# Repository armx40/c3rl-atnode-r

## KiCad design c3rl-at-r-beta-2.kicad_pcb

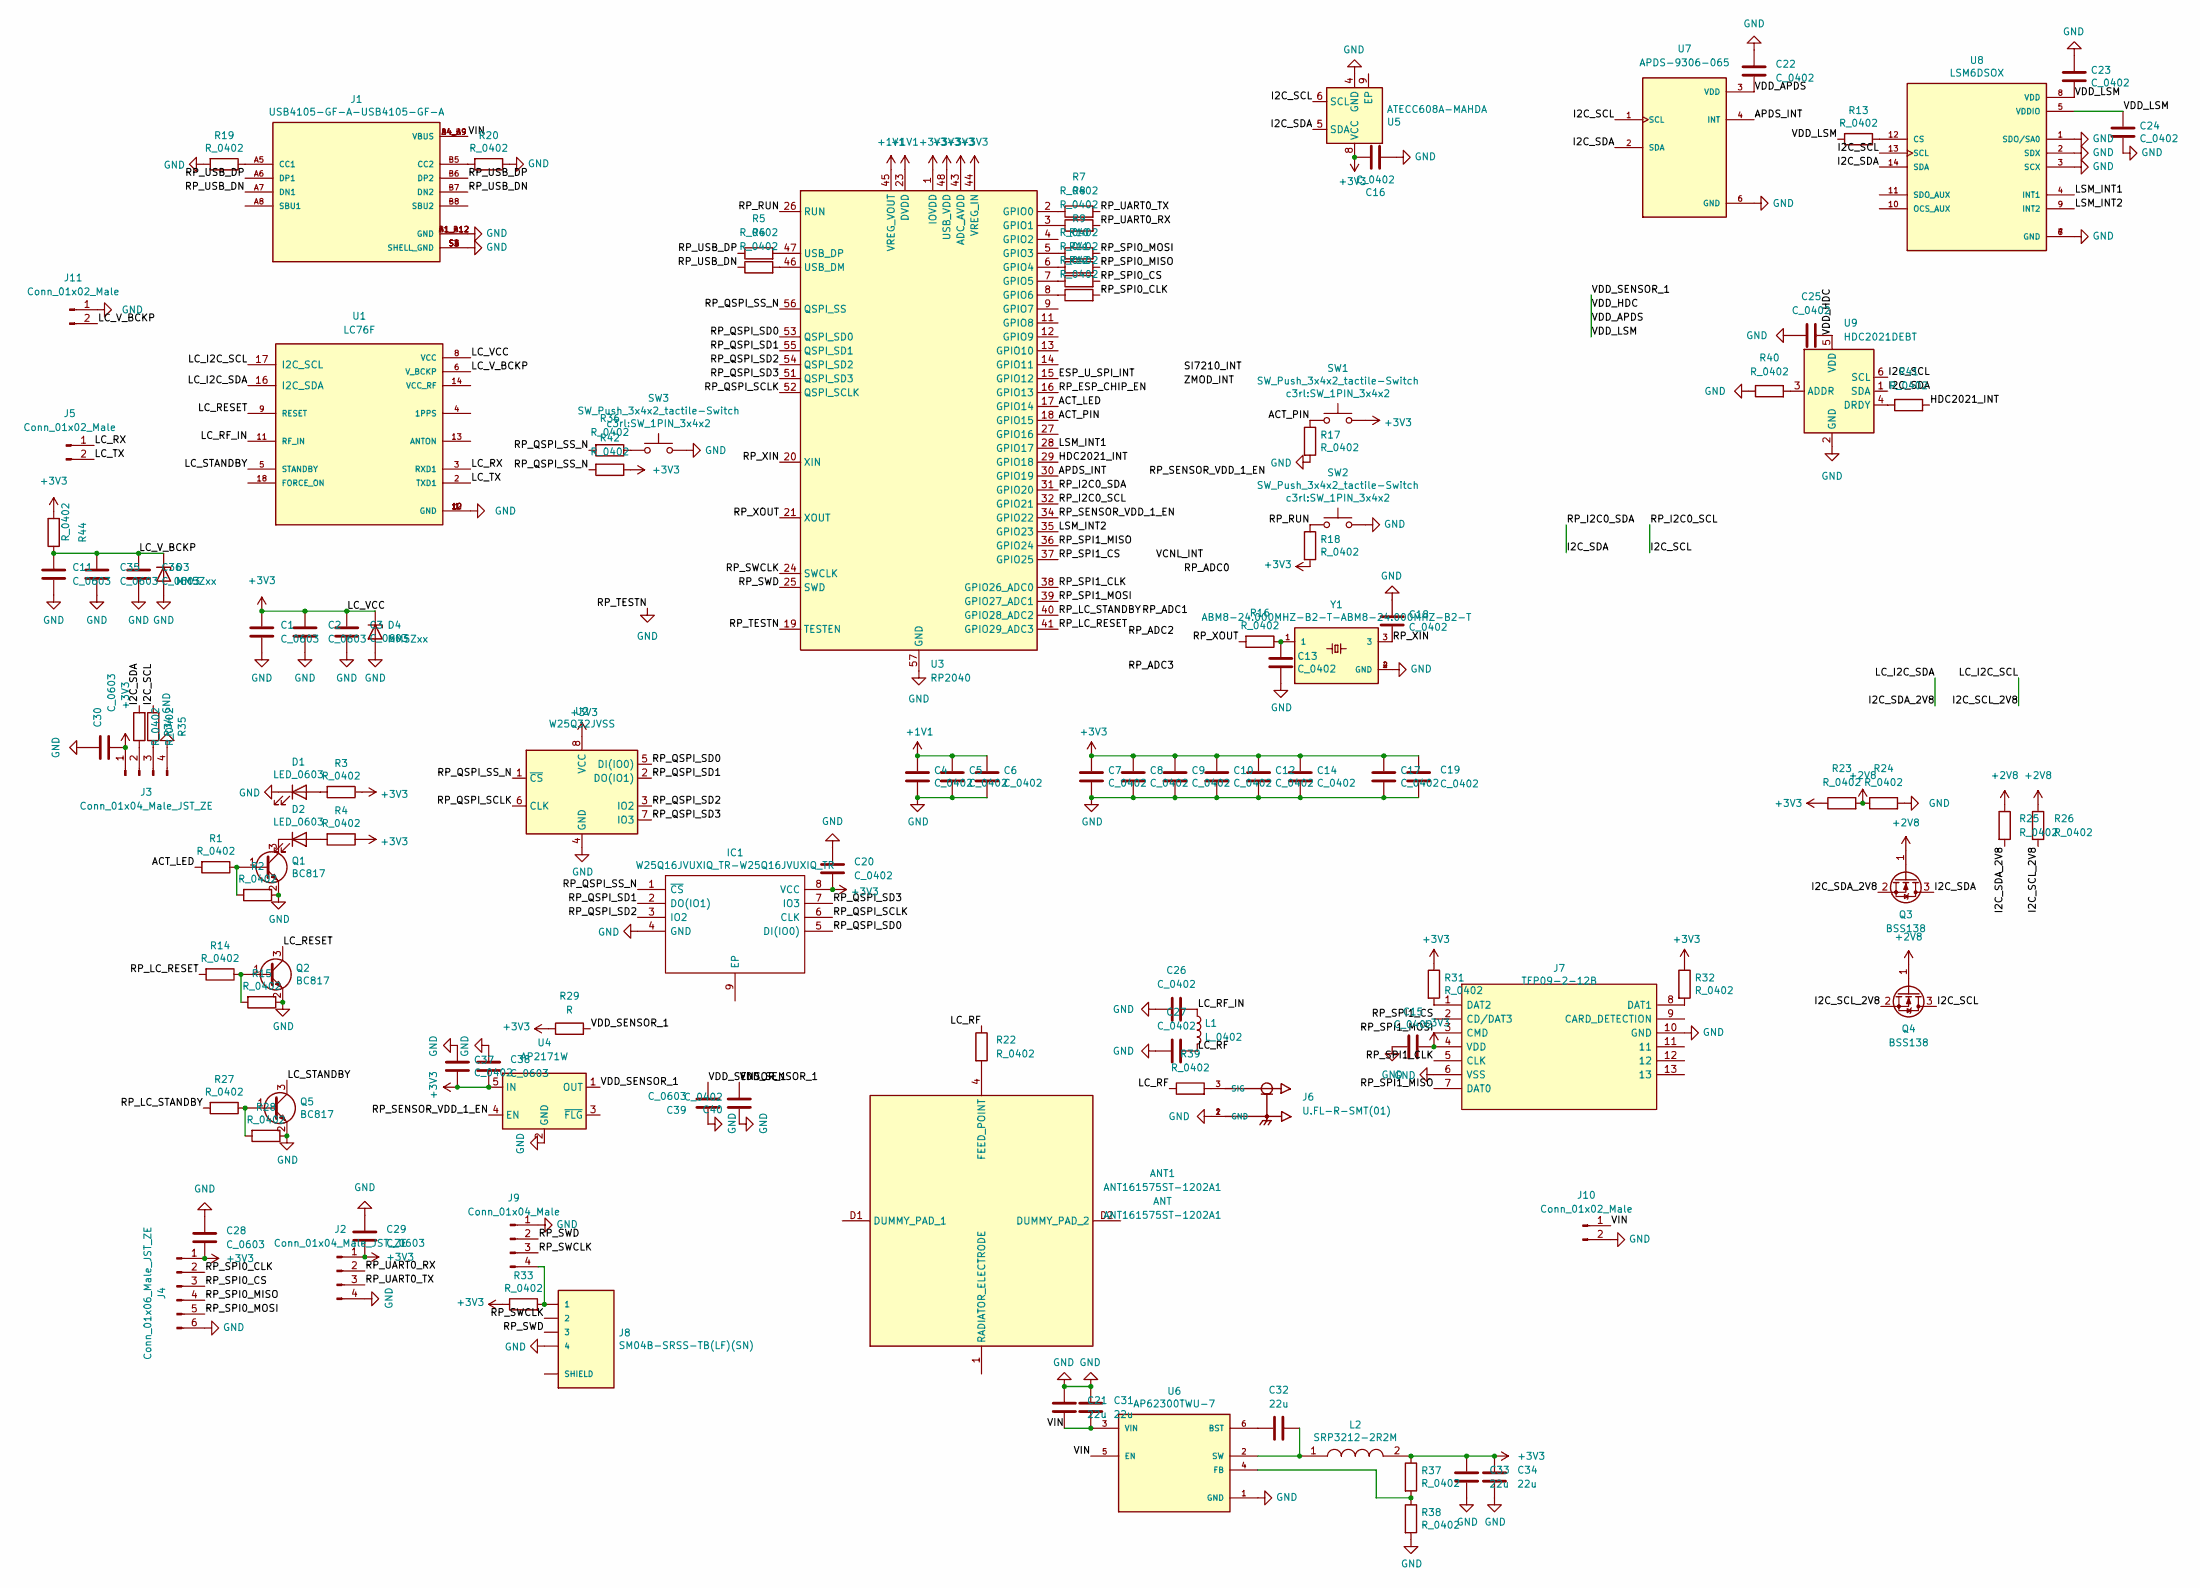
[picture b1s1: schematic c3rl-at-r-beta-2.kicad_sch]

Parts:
ANT1: ANT161575ST-1202A1; ANT161575ST1202A1; Manufacturer_Part_Number ANT161575ST-1202A1; Mouser Part Number 810-ANT161575ST1202A
C1, C11, C28, C29, C30, C38, C39: C_0603; C_0603_1608Metric
C2, C3, C35, C36: C_0603; C_0402_1005Metric
C4, C5, C6, C7, C8, C9, C10, C12, C13, C14, C15, C16, C17, C18, C19, C20, C22, C23, C24, C25, C26, C27, C37, C40: C_0402; C_0402_1005Metric
C21, C31, C32, C33, C34: 22u; C_0603_1608Metric
D1, D2: LED_0603; LED_0603_1608Metric
D3, D4: MM5Zxx; D_SOD-523
IC1: W25Q16JVUXIQ_TR-W25Q16JVUXIQ_TR; SON50P300X200X60-9N; Manufacturer_Part_Number W25Q16JVUXIQ TR; Mouser Part Number 454-W25Q16JVUXIQTR
J1: USB4105-GF-A-USB4105-GF-A; GCT_USB4105-GF-A; PARTREV A3
J2, J3: Conn_01x04_Male_JST_ZE; JST_ZE_B04B-ZESK-D_1x04_P1.50mm_Vertical
J4: Conn_01x06_Male_JST_ZE; JST_ZE_B06B-ZESK-D_1x06_P1.50mm_Vertical
J5: Conn_01x02_Male; PinHeader_1x02_P1.27mm_Vertical
J6: U.FL-R-SMT(01); HRS_U.FL-R-SMT(01)
J7: TFP09-2-12B; TFP09212B; Manufacturer_Part_Number TFP09-2-12B
J8: SM04B-SRSS-TB(LF)(SN); JST_SM04B-SRSS-TB(LF)(SN)
J9: Conn_01x04_Male; PinHeader_1x04_P1.27mm_Vertical
J10: Conn_01x02_Male; JST_PH_S2B-PH-SM4-TB_1x02-1MP_P2.00mm_Horizontal
J11: Conn_01x02_Male; PinHeader_1x02_P2.00mm_Vertical
L1: L_0402; L_0402_1005Metric
L2: SRP3212-2R2M; INDC2520X100N; Manufacturer_Part_Number SRP3212-2R2M
Q1, Q2, Q5: BC817; SOT-23
Q3, Q4: BSS138; SOT-23
R1, R2, R3, R4, R5, R6, R7, R8, R9, R10, R11, R12, R13, R14, R15, R16, R17, R18, R19, R20, R22, R23, R24, R25, R26, R27, R28, R31, R32, R33, R34, R35, R36, R37, R38, R39, R40, R41, R42, R44: R_0402; R_0402_1005Metric
R29: R; R_0402_1005Metric
SW1, SW2, SW3: SW_Push_3x4x2_tactile-Switch; SW_1PIN_3x4x2
U1: LC76F; XCVR_L76LBA31
U2: W25Q32JVSS; SOIC-8_5.23x5.23mm_P1.27mm
U3: RP2040; QFN-56-1EP_7x7mm_P0.4mm_EP3.2x3.2mm
U4: AP2171W; SOT-23-5
U5: ATECC608A-MAHDA; DFN-8-1EP_3x2mm_P0.5mm_EP1.3x1.5mm
U6: AP62300TWU-7; SOT95P280X100-6N; PARTREV Rev. 3 - 2
U7: APDS-9306-065; SON65P200X200X75-6N
U8: LSM6DSOX; PQFN50P250X300X86-14N; PARTREV 3.0
U9: HDC2021DEBT; PHDC2021DEBT
Y1: ABM8-24.000MHZ-B2-T-ABM8-24.000MHZ-B2-T; OSCSC320X250X100N

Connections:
+1V1: C4.1, C5.1, C6.1, U3.23 (DVDD), U3.45 (VREG_VOUT), U3.50 (DVDD)
+2V8: Q3.1 (G), Q4.1 (G), R23.2, R24.1, R25.1, R26.1
+3V3: C1.1, C2.1, C3.1, C7.1, C8.1, C9.1, C10.1, C12.1, C14.1, C15.1, C16.2, C17.1, C19.1, C20.2, C28.2, C29.2, C30.2, C33.1, C34.1, C37.1, C38.2, D4.1 (K), IC1.8 (VCC), J2.1, J3.1, J4.1, J7.4 (VDD), L2.2, R3.1, R4.1, R18.2, R23.1, R29.1, R31.1, R32.1, R33.1, R37.1, R42.1, R44.2, SW1.2, U1.8 (VCC), U2.8 (VCC), U3.1 (IOVDD), U3.10 (IOVDD), U3.22 (IOVDD), U3.33 (IOVDD), U3.42 (IOVDD), U3.43 (ADC_AVDD), U3.44 (VREG_IN), U3.48 (USB_VDD), U3.49 (IOVDD), U4.5 (IN), U5.8 (VCC)
/ACT_LED: R1.2, U3.17 (GPIO14)
/ACT_PIN: R17.1, SW1.1, U3.18 (GPIO15)
/APDS_INT: U3.30 (GPIO19), U7.4 (INT)
/ESP_U_SPI_INT: U3.15 (GPIO12)
/HDC2021_INT: R41.2, U3.29 (GPIO18)
/I2C_SCL: Q4.3 (D), R35.2, U3.32 (GPIO21), U5.6 (SCL), U7.1 (SCL), U8.13 (SCL), U9.6 (SCL)
/I2C_SCL_2V8: Q4.2 (S), R26.2, U1.17 (I2C_SCL)
/I2C_SDA: Q3.3 (D), R34.2, U3.31 (GPIO20), U5.5 (SDA), U7.2 (SDA), U8.14 (SDA), U9.1 (SDA)
/I2C_SDA_2V8: Q3.2 (S), R25.2, U1.16 (I2C_SDA)
/LC_RESET: Q2.3 (C), U1.9 (RESET)
/LC_RF: C27.2, L1.2, R22.1, R39.1
/LC_RF_IN: C26.2, L1.1, U1.11 (RF_IN)
/LC_RX: J5.1, U1.3 (RXD1)
/LC_STANDBY: Q5.3 (C), U1.5 (STANDBY)
/LC_TX: J5.2, U1.2 (TXD1)
/LC_V_BCKP: C11.1, C35.1, C36.1, D3.1 (K), J11.2, R44.1, U1.6 (V_BCKP)
/LSM_INT1: U3.28 (GPIO17), U8.4 (INT1)
/LSM_INT2: U3.35 (GPIO23), U8.9 (INT2)
/RP_ESP_CHIP_EN: U3.16 (GPIO13)
/RP_LC_RESET: R14.2, U3.41 (GPIO29_ADC3)
/RP_LC_STANDBY: R27.2, U3.40 (GPIO28_ADC2)
/RP_QSPI_SCLK: IC1.6 (CLK), U2.6 (CLK), U3.52 (QSPI_SCLK)
/RP_QSPI_SD0: IC1.5 (DI(IO0)), U2.5 (DI(IO0)), U3.53 (QSPI_SD0)
/RP_QSPI_SD1: IC1.2 (DO(IO1)), U2.2 (DO(IO1)), U3.55 (QSPI_SD1)
/RP_QSPI_SD2: IC1.3 (IO2), U2.3 (IO2), U3.54 (QSPI_SD2)
/RP_QSPI_SD3: IC1.7 (IO3), U2.7 (IO3), U3.51 (QSPI_SD3)
/RP_QSPI_SS_N: IC1.1 (~CS), R36.2, R42.2, U2.1 (~CS), U3.56 (QSPI_SS)
/RP_RUN: R18.1, SW2.1, U3.26 (RUN)
/RP_SENSOR_VDD_1_EN: U3.34 (GPIO22), U4.4 (EN)
/RP_SPI0_CLK: J4.2, R12.2
/RP_SPI0_CS: J4.3, R11.2
/RP_SPI0_MISO: J4.4, R10.2
/RP_SPI0_MOSI: J4.5, R9.2
/RP_SPI1_CLK: J7.5 (CLK), U3.38 (GPIO26_ADC0)
/RP_SPI1_CS: J7.2 (CD/DAT3), U3.37 (GPIO25)
/RP_SPI1_MISO: J7.7 (DAT0), U3.36 (GPIO24)
/RP_SPI1_MOSI: J7.3 (CMD), U3.39 (GPIO27_ADC1)
/RP_SWCLK: J8.2, J9.3, U3.24 (SWCLK)
/RP_SWD: J8.3, J9.2, U3.25 (SWD)
/RP_UART0_RX: J2.2, R8.2
/RP_UART0_TX: J2.3, R7.2
/RP_USB_DN: J1.A7 (DN1), J1.B7 (DN2), R6.1
/RP_USB_DP: J1.A6 (DP1), J1.B6 (DP2), R5.1
/RP_XIN: C18.2, U3.20 (XIN), Y1.3
/RP_XOUT: R16.2, U3.21 (XOUT)
/VDD_APDS: C22.2, C23.2, C24.1, C25.2, C39.2, C40.1, R13.2, R29.2, U4.1 (OUT), U7.3 (VDD), U8.5 (VDDIO), U8.8 (VDD), U9.5 (VDD)
/VIN: C21.2, C31.2, J1.A4_B9 (VBUS), J1.B4_A9 (VBUS), J10.1, U6.3 (VIN), U6.5 (EN)
GND: C1.2, C2.2, C3.2, C4.2, C5.2, C6.2, C7.2, C8.2, C9.2, C10.2, C11.2, C12.2, C13.1, C14.2, C15.2, C16.1, C17.2, C18.1, C19.2, C20.1, C21.1, C22.1, C23.1, C24.2, C25.1, C26.1, C27.1, C28.1, C29.1, C30.1, C31.1, C33.2, C34.2, C35.2, C36.2, C37.2, C38.1, C39.1, C40.2, D1.1 (K), D3.2 (A), D4.2 (A), IC1.4 (GND), J1.A1_B12 (GND), J1.B1_A12 (GND), J1.S1 (SHELL_GND), J1.S2 (SHELL_GND), J1.S3 (SHELL_GND), J1.S4 (SHELL_GND), J2.4, J3.4, J4.6, J6.1 (GND), J6.2 (GND), J7.6 (VSS), J7.10 (GND), J8.4, J9.1, J10.2, J11.1, Q1.2 (E), Q2.2 (E), Q5.2 (E), R2.1, R15.1, R17.2, R19.2, R20.1, R24.2, R28.1, R38.2, R40.1, SW2.2, SW3.2, U1.1 (GND), U1.10 (GND), U1.12 (GND), U2.4 (GND), U3.19 (TESTEN), U3.57 (GND), U4.2 (GND), U5.4 (GND), U6.1 (GND), U7.6 (GND), U8.1 (SDO/SA0), U8.2 (SDX), U8.3 (SCX), U8.6 (GND), U8.7 (GND), U9.2 (GND), Y1.2 (GND), Y1.4 (GND)
unnamed: ANT1.4 (FEED_POINT), R22.2
unnamed: C13.2, R16.1, Y1.1
unnamed: C32.1, U6.6 (BST)
unnamed: C32.2, L2.1, U6.2 (SW)
unnamed: D1.2 (A), R3.2
unnamed: D2.1 (K), Q1.3 (C)
unnamed: D2.2 (A), R4.2
unnamed: J1.A5 (CC1), R19.1
unnamed: J1.B5 (CC2), R20.2
unnamed: J3.2, R34.1
unnamed: J3.3, R35.1
unnamed: J6.3 (SIG), R39.2
unnamed: J7.1 (DAT2), R31.2
unnamed: J7.8 (DAT1), R32.2
unnamed: J8.1, J9.4, R33.2
unnamed: J8.S1 (SHIELD), J8.S2 (SHIELD)
unnamed: Q1.1 (B), R1.1, R2.2
unnamed: Q2.1 (B), R14.1, R15.2
unnamed: Q5.1 (B), R27.1, R28.2
unnamed: R5.2, U3.47 (USB_DP)
unnamed: R6.2, U3.46 (USB_DM)
unnamed: R7.1, U3.2 (GPIO0)
unnamed: R8.1, U3.3 (GPIO1)
unnamed: R9.1, U3.5 (GPIO3)
unnamed: R10.1, U3.6 (GPIO4)
unnamed: R11.1, U3.7 (GPIO5)
unnamed: R12.1, U3.8 (GPIO6)
unnamed: R13.1, U8.12 (CS)
unnamed: R36.1, SW3.1
unnamed: R37.2, R38.1, U6.4 (FB)
unnamed: R40.2, U9.3 (ADDR)
unnamed: R41.1, U9.4 (DRDY)

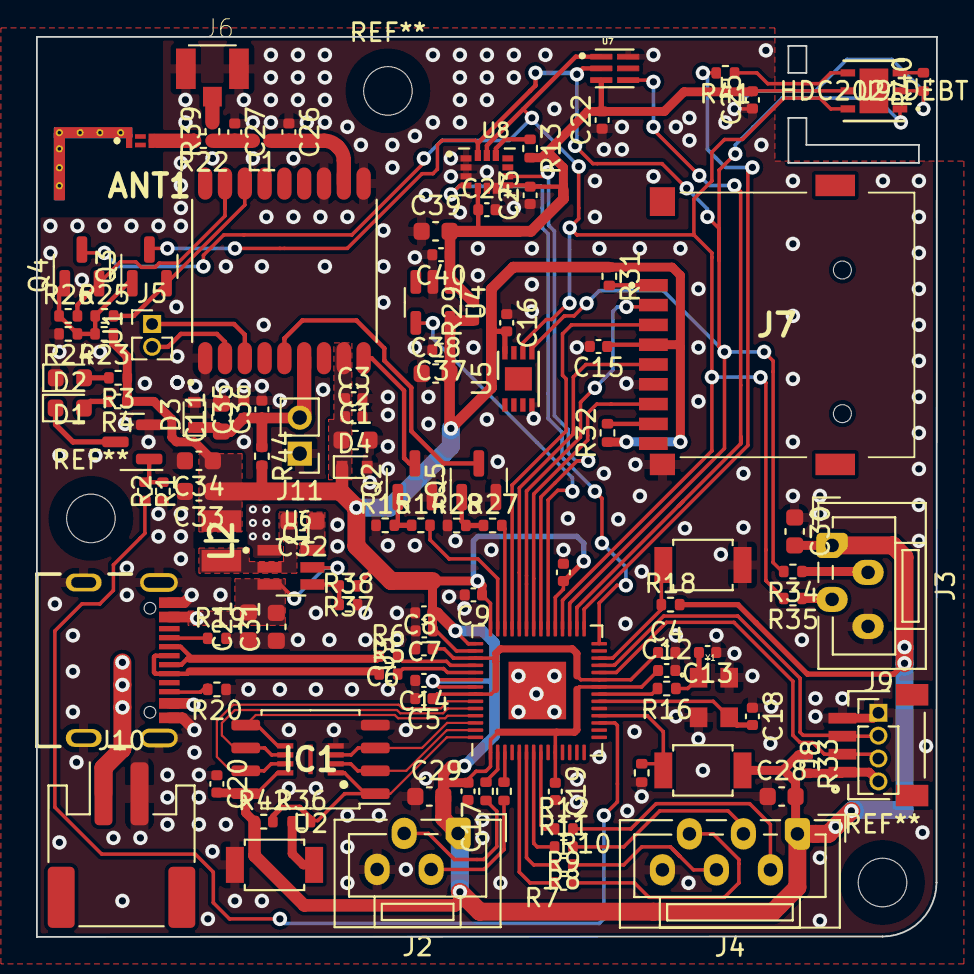
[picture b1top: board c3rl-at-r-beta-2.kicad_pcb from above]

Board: 2 copper layers, 50.0 x 50.0 mm, 118 parts (0 on the bottom side), 81 nets.

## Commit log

2023-10-26 init
2023-10-26 bigger width
2023-11-19 rev 1

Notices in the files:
parts and their libraries:
Copyright 2016 Accelerated Designs. All rights reserved.
